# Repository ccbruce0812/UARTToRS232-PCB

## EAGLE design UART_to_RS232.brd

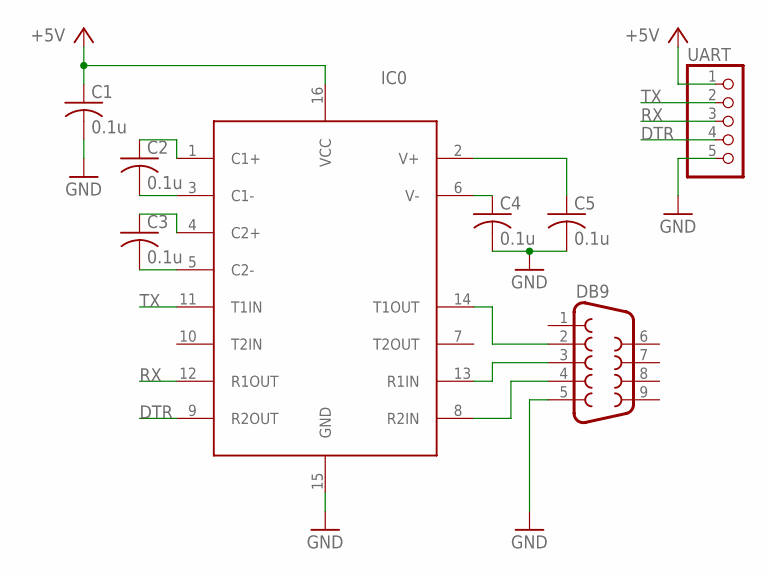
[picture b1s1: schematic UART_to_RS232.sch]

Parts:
C1, C2, C3, C4, C5: 0.1u; C0805K
DB9: F09HP
IC0: ICL3232; SO16
UART: PINHD-1X5; 1X05

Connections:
+5V: C1.1, IC0.16 (VCC), UART.1
DTR: IC0.9 (R2OUT), UART.4
GND: C1.2, C4.2, C5.2, DB9.5, IC0.15 (GND), UART.5
unnamed: C3.2, IC0.5 (C2-)
unnamed: C3.1, IC0.4 (C2+)
unnamed: C2.1, IC0.1 (C1+)
unnamed: C2.2, IC0.3 (C1-)
unnamed: C5.1, IC0.2 (V+)
unnamed: C4.1, IC0.6 (V-)
unnamed: DB9.2, IC0.14 (T1OUT)
unnamed: DB9.3, IC0.13 (R1IN)
unnamed: DB9.4, IC0.8 (R2IN)
RX: IC0.12 (R1OUT), UART.3
TX: IC0.11 (T1IN), UART.2

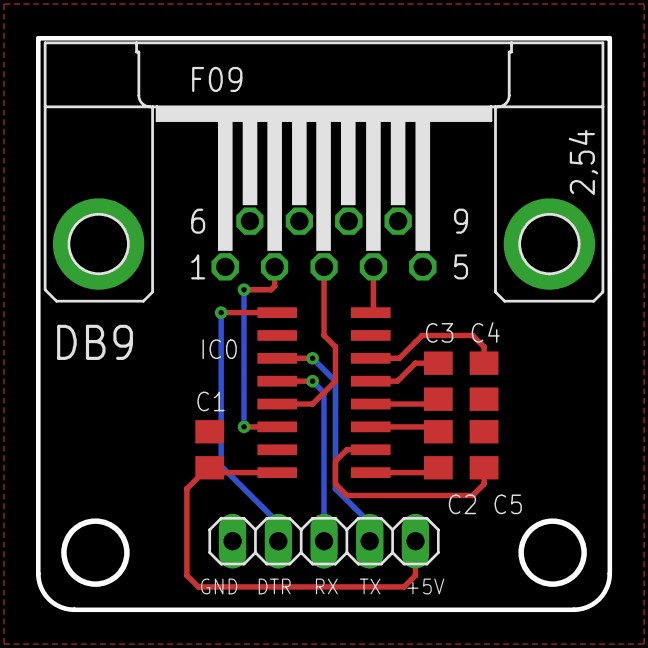
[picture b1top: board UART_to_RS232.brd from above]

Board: 2 copper layers, 31.7 x 31.7 mm, 8 parts (0 on the bottom side), 14 nets.

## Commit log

2018-06-24 Draft version.
